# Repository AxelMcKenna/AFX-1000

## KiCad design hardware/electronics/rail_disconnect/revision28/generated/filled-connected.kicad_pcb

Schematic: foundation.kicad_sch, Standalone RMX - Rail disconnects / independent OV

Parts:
C1, C5, C9, C13, C17, C21, C25, C29, C34, C35, C36, C37: 100nF 16V X7R; C_0805_2012Metric
C2, C3, C6, C7, C10, C11, C14, C15, C18, C19, C22, C23: 10pF 100V C0G 5%; C_0805_2012Metric
C4, C8: 1500uF 35V electrolytic 20% EEUFR1V152S; CP_Radial_D16.0mm_P7.50mm
C12, C16: 220uF 35V electrolytic 20% EEUFR1V221; CP_Radial_D8.0mm_P3.50mm
C20: 1500uF 16V electrolytic 20% EEUFR1C152; CP_Radial_D10.0mm_P5.00mm
C24: 4700uF 16V electrolytic 20% EEUFR1C472; CP_Radial_D16.0mm_P7.50mm
C26: 1uF 16V X7R; C_0805_2012Metric
C27, C28, C30, C31, C32, C33: 100pF 50V C0G 5%; C_0805_2012Metric
C38: 10uF 16V X7R; C_0805_2012Metric
J1, J3: Header6; PinHeader_1x06_P2.54mm_Vertical
J2, J4: Header2; PinHeader_1x02_P2.54mm_Vertical
J5, J6: Header3; PinHeader_1x03_P2.54mm_Vertical
J7, J8: 7466003R; 7466003R_M3_SMT_Annulus_NPTH
Q1, Q2, Q3, Q4, Q5, Q6, Q7, Q8: CSD18540Q5B; CSD18540Q5B_TI_Q5B
Q9, Q10, Q11, Q12, Q13, Q14: CSD18510Q5B; CSD18510Q5B_TI_Q5B
R1, R9, R17, R25, R33, R41: 22 1%; R_0805_2012Metric
R2, R10, R18, R26, R34, R42, R60, R63, R68, R71, R76, R81, R86, R91: 20M 1%; R_0805_2012Metric
R3, R5, R11, R13, R19, R21, R27, R29, R35, R37, R43, R45, R61, R64, R69, R72, R77, R82, R87, R92: 10k 1%; R_0805_2012Metric
R4, R12, R20, R28, R36, R44: 100 1%; R_0805_2012Metric
R6, R7, R14, R15, R22, R23, R30, R31, R38, R39, R46, R47: 15k 1%; R_0805_2012Metric
R8, R16, R24, R32, R40, R48: 47k 1%; R_0805_2012Metric
R49: 150k 0.01% 5ppm; R_0805_2012Metric
R50: 6.2k 0.01% 5ppm; R_0805_2012Metric
R51, R54, R58, R59, R62, R66, R67, R70, R74, R75, R79, R80, R84, R85, R89, R90, R94: 10k 0.01% 5ppm; R_0805_2012Metric
R52, R55: 1k 1%; R_0805_2012Metric
R53: 100k 0.01% 5ppm; R_0805_2012Metric
R56: 143k 0.01% 5ppm; R_0805_2012Metric
R57: 3.3k 0.01% 5ppm; R_0805_2012Metric
R65: 90.9k 0.01% 5ppm; R_0805_2012Metric
R73, R78: 31.6k 0.01% 5ppm; R_0805_2012Metric
R83: 12.4k 0.01% 5ppm; R_0805_2012Metric
R88: 7.5k 0.01% 5ppm; R_0805_2012Metric
R93: 100k 1%; R_0805_2012Metric
U1, U2, U3, U4, U5, U6: SI8751AB-ISR; SOIC-8_3.9x4.9mm_P1.27mm
U7: REF35125QDBVR; SOT-23-6
U8: OPA2333AID; SOIC-8_3.9x4.9mm_P1.27mm
U9, U10: TLV1824IDR; SOIC-14_3.9x8.7mm_P1.27mm
U11, U12: SN74LVC08APWR; TSSOP-14_4.4x5mm_P0.65mm

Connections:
/5V_DIG: C24.1, J4.1 (5V_DIG), Q12.3 (DRAIN_GROUP), Q14.3 (DRAIN_GROUP), R47.1, R48.1
/5V_DIG_ALLOW: R44.2, R45.1, U6.3 (IN)
/5V_DIG_COMMON: Q11.1 (SOURCE_GROUP), Q12.1 (SOURCE_GROUP), Q13.1 (SOURCE_GROUP), Q14.1 (SOURCE_GROUP), R42.2, U6.5 (SOURCE)
/5V_DIG_DRIVE: R41.1, U6.8 (GATE)
/5V_DIG_GATE: Q11.2 (GATE_GROUP), Q12.2 (GATE_GROUP), Q13.2 (GATE_GROUP), Q14.2 (GATE_GROUP), R41.2, R42.1
/5V_DIG_MCAP1: C22.2, U6.7 (MCAP1)
/5V_DIG_MCAP1_LIMIT: C22.1, R46.2
/5V_DIG_MCAP2: C23.2, U6.6 (MCAP2)
/5V_DIG_MCAP2_LIMIT: C23.1, R47.2
/5V_DIG_OV_OK: R81.1, R82.2, U10.1 (2OUT), U11.10 (3B)
/5V_DIG_OV_REF: R80.2, R81.2, U10.7 (2+)
/5V_DIG_OV_SENSE: C33.1, R78.2, R79.1, U10.6 (2-)
/5V_DIG_SRC: J2.1 (5V_DIG_SRC), Q11.3 (DRAIN_GROUP), Q13.3 (DRAIN_GROUP), R46.1, R78.1
/5V_DIG_TT: R43.1, U6.2 (TT)
/AGND: C1.2, C4.2, C5.2, C8.1, C9.2, C12.2, C13.2, C16.1, C17.2, C20.2, C21.2, C24.2, C25.2, C26.2, C27.2, C28.2, C29.2, C30.2, C31.2, C32.2, C33.2, C34.2, C35.2, C36.2, C37.2, C38.2, J1.2 (AGND), J2.2 (AGND), J3.2 (AGND), J4.2 (AGND), J5.2 (AGND), J6.1 (AGND), J7.1, J8.1, R3.2, R5.2, R8.2, R11.2, R13.2, R16.2, R19.2, R21.2, R24.2, R27.2, R29.2, R32.2, R35.2, R37.2, R40.2, R43.2, R45.2, R48.2, R58.2, R66.2, R74.2, R79.2, R84.2, R89.2, R93.2, R94.2, U1.4 (GND), U2.4 (GND), U3.4 (GND), U4.4 (GND), U5.4 (GND), U6.4 (GND), U7.1 (GND), U7.2 (GND), U8.3 (IN+_A), U8.4 (V-), U8.5 (IN+_B), U9.12 (V-), U10.12 (V-), U11.7 (GND), U12.7 (GND)
/ALL_RAILS_ALLOW: J6.2 (ALL_RAILS_ALLOW), R4.1, R12.1, R20.1, R28.1, R36.1, R44.1, U12.11 (4Y)
/N12: C16.2, J3.5 (N12), Q8.3 (DRAIN_GROUP), R31.1, R32.1
/N12_ALLOW: R28.2, R29.1, U4.3 (IN)
/N12_COMMON: Q7.1 (SOURCE_GROUP), Q8.1 (SOURCE_GROUP), R26.2, U4.5 (SOURCE)
/N12_DRIVE: R25.1, U4.8 (GATE)
/N12_GATE: Q7.2 (GATE_GROUP), Q8.2 (GATE_GROUP), R25.2, R26.1
/N12_INV: R54.1, R55.1, U8.7 (OUT_B)
/N12_MCAP1: C14.2, U4.7 (MCAP1)
/N12_MCAP1_LIMIT: C14.1, R30.2
/N12_MCAP2: C15.2, U4.6 (MCAP2)
/N12_MCAP2_LIMIT: C15.1, R31.2
/N12_OV_OK: R71.1, R72.2, U9.13 (4OUT), U11.5 (2B)
/N12_OV_REF: R70.2, R71.2, U9.11 (4+)
/N12_OV_SENSE: C28.1, R55.2, U9.10 (4-)
/N12_SRC: J1.5 (N12_SRC), Q7.3 (DRAIN_GROUP), R30.1, R53.1
/N12_SUM: R53.2, R54.2, U8.6 (IN-_B)
/N12_TT: R27.1, U4.2 (TT)
/N19: C8.2, J3.3 (N19), Q4.3 (DRAIN_GROUP), R15.1, R16.1
/N19_ALLOW: R12.2, R13.1, U2.3 (IN)
/N19_COMMON: Q3.1 (SOURCE_GROUP), Q4.1 (SOURCE_GROUP), R10.2, U2.5 (SOURCE)
/N19_DRIVE: R9.1, U2.8 (GATE)
/N19_GATE: Q3.2 (GATE_GROUP), Q4.2 (GATE_GROUP), R9.2, R10.1
/N19_INPUT_MID: R49.2, R50.1
/N19_INV: R51.1, R52.1, U8.1 (OUT_A)
/N19_MCAP1: C6.2, U2.7 (MCAP1)
/N19_MCAP1_LIMIT: C6.1, R14.2
/N19_MCAP2: C7.2, U2.6 (MCAP2)
/N19_MCAP2_LIMIT: C7.1, R15.2
/N19_OV_OK: R63.1, R64.2, U9.1 (2OUT), U11.2 (1B)
/N19_OV_REF: R62.2, R63.2, U9.7 (2+)
/N19_OV_SENSE: C27.1, R52.2, U9.6 (2-)
/N19_SRC: J1.3 (N19_SRC), Q3.3 (DRAIN_GROUP), R14.1, R49.1
/N19_SUM: R50.2, R51.2, U8.2 (IN-_A)
/N19_TT: R11.1, U2.2 (TT)
/OK_5: U11.8 (3Y), U12.4 (2A)
/OK_12: U11.6 (2Y), U12.2 (1B)
/OK_19: U11.3 (1Y), U12.1 (1A)
/OK_ALL_OV: U12.8 (3Y), U12.12 (4A)
/OK_ANALOG: U12.3 (1Y), U12.9 (3A)
/OK_AUXILIARY: U12.6 (2Y), U12.10 (3B)
/OK_REF: U11.11 (4Y), U12.5 (2B)
/P12: C12.1, J3.4 (P12), Q6.3 (DRAIN_GROUP), R23.1, R24.1
/P12_ALLOW: R20.2, R21.1, U3.3 (IN)
/P12_COMMON: Q5.1 (SOURCE_GROUP), Q6.1 (SOURCE_GROUP), R18.2, U3.5 (SOURCE)
/P12_DRIVE: R17.1, U3.8 (GATE)
/P12_GATE: Q5.2 (GATE_GROUP), Q6.2 (GATE_GROUP), R17.2, R18.1
/P12_MCAP1: C10.2, U3.7 (MCAP1)
/P12_MCAP1_LIMIT: C10.1, R22.2
/P12_MCAP2: C11.2, U3.6 (MCAP2)
/P12_MCAP2_LIMIT: C11.1, R23.2
/P12_OV_OK: R68.1, R69.2, U9.14 (3OUT), U11.4 (2A)
/P12_OV_REF: R67.2, R68.2, U9.9 (3+)
/P12_OV_SENSE: C31.1, R65.2, R66.1, U9.8 (3-)
/P12_SRC: J1.4 (P12_SRC), Q5.3 (DRAIN_GROUP), R22.1, R65.1
/P12_TT: R19.1, U3.2 (TT)
/P19: C4.1, J3.1 (P19), Q2.3 (DRAIN_GROUP), R7.1, R8.1
/P19_ALLOW: R4.2, R5.1, U1.3 (IN)
/P19_COMMON: Q1.1 (SOURCE_GROUP), Q2.1 (SOURCE_GROUP), R2.2, U1.5 (SOURCE)
/P19_DRIVE: R1.1, U1.8 (GATE)
/P19_GATE: Q1.2 (GATE_GROUP), Q2.2 (GATE_GROUP), R1.2, R2.1
/P19_MCAP1: C2.2, U1.7 (MCAP1)
/P19_MCAP1_LIMIT: C2.1, R6.2
/P19_MCAP2: C3.2, U1.6 (MCAP2)
/P19_MCAP2_LIMIT: C3.1, R7.2
/P19_OV_OK: R60.1, R61.2, U9.2 (1OUT), U11.1 (1A)
/P19_OV_REF: R59.2, R60.2, U9.5 (1+)
/P19_OV_SENSE: C30.1, R57.2, R58.1, U9.4 (1-)
/P19_SENSE_MID: R56.2, R57.1
/P19_SRC: J1.1 (P19_SRC), Q1.3 (DRAIN_GROUP), R6.1, R56.1
/P19_TT: R3.1, U1.2 (TT)
/POWER_RUN: J5.3 (POWER_RUN), R93.1, U12.13 (4B)
/PROTECT_REF: C26.1, J6.3 (PROTECT_REF), R59.1, R62.1, R67.1, R70.1, R75.1, R80.1, R85.1, R94.1, U7.6 (VREF), U10.10 (4-)
/REF_HIGH_AUX: R88.2, R89.1, R90.1
/REF_HIGH_OK: R91.1, R92.2, U10.13 (4OUT), U11.13 (4B)
/REF_HIGH_POSITIVE: R90.2, R91.2, U10.11 (4+)
/REF_LOW_AUX: R83.2, R84.1, U10.8 (3-)
/REF_LOW_OK: R86.1, R87.2, U10.14 (3OUT), U11.12 (4A)
/REF_LOW_POSITIVE: R85.2, R86.2, U10.9 (3+)
/V2V5_AUX: C1.1, C5.1, C9.1, C13.1, C17.1, C21.1, C25.1, C29.1, C34.1, C35.1, C36.1, C37.1, C38.1, J5.1 (V2V5_AUX), R61.1, R64.1, R69.1, R72.1, R77.1, R82.1, R83.1, R87.1, R88.1, R92.1, U1.1 (VDD), U2.1 (VDD), U3.1 (VDD), U4.1 (VDD), U5.1 (VDD), U6.1 (VDD), U7.3 (EN), U7.4 (VIN), U8.8 (V+), U9.3 (V+), U10.3 (V+), U11.14 (VCC), U12.14 (VCC)
/V5_REG: C20.1, J3.6 (V5_REG), Q10.3 (DRAIN_GROUP), R39.1, R40.1
/V5_REG_ALLOW: R36.2, R37.1, U5.3 (IN)
/V5_REG_COMMON: Q9.1 (SOURCE_GROUP), Q10.1 (SOURCE_GROUP), R34.2, U5.5 (SOURCE)
/V5_REG_DRIVE: R33.1, U5.8 (GATE)
/V5_REG_GATE: Q9.2 (GATE_GROUP), Q10.2 (GATE_GROUP), R33.2, R34.1
/V5_REG_MCAP1: C18.2, U5.7 (MCAP1)
/V5_REG_MCAP1_LIMIT: C18.1, R38.2
/V5_REG_MCAP2: C19.2, U5.6 (MCAP2)
/V5_REG_MCAP2_LIMIT: C19.1, R39.2
/V5_REG_OV_OK: R76.1, R77.2, U10.2 (1OUT), U11.9 (3A)
/V5_REG_OV_REF: R75.2, R76.2, U10.5 (1+)
/V5_REG_OV_SENSE: C32.1, R73.2, R74.1, U10.4 (1-)
/V5_REG_SRC: J1.6 (V5_REG_SRC), Q9.3 (DRAIN_GROUP), R38.1, R73.1
/V5_REG_TT: R35.1, U5.2 (TT)

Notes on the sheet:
E17: six common-source FET rail disconnects; AUX-powered precision OV sensing and all-rail interlock. Source rails and protected outputs are distinct nets.
Candidate schematic only. No routed board,complete enclosure fit,manufacturer transient/stability model or physical protection proof.
Any source OV/reference-window fault or POWER_RUN low disables all six drivers. Zero source voltage is allowed during startup; no protected-rail supply dependency.
VSONP grouped pads1=S(physical1..3),2=G(physical4),3=D(physical5..8/EP). Body diodes oppose. Gate/source reference floats with each common node.
Si8751 timing maxima use100pF load. Actual FET charge,bulk capacitors,MCAP currents,inrush,leakage,partial-power and fault-energy limits require qualification.

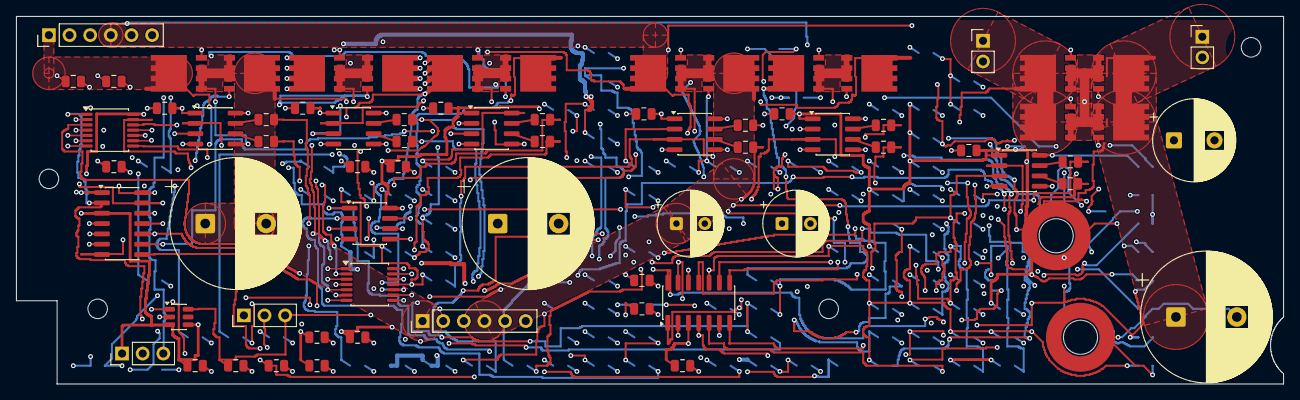
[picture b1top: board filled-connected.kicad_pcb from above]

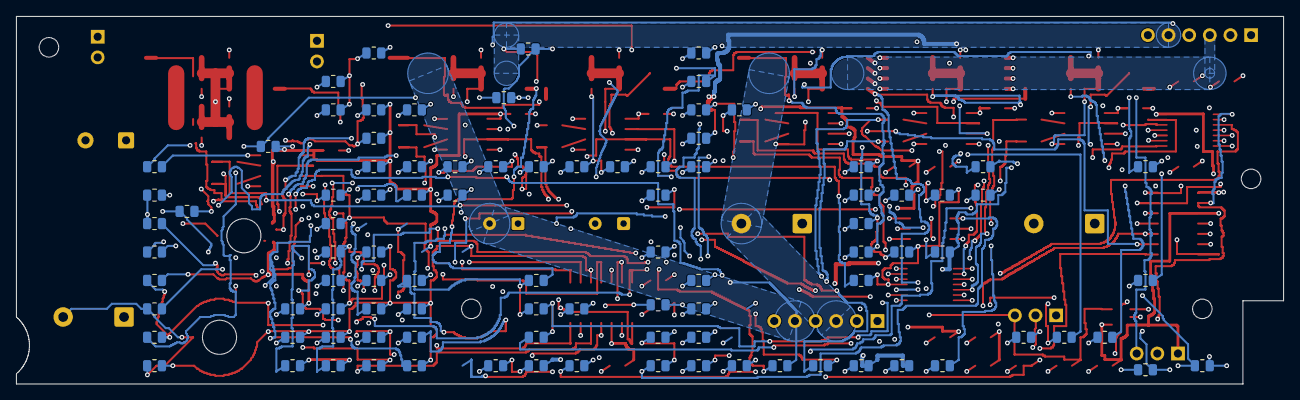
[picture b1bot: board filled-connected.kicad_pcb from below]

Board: 6 copper layers, 156.0 x 45.2 mm, 170 parts (94 on the bottom side), 108 nets.

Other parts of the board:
H1, H2, H3, H4: M2_CLEARANCE; M2_Clearance
